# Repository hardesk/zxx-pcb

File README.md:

# Caravel with Z80 to DIP40 adapter PCB

See: https://github.com/rejunity/z80-open-silicon

## Pinout

                                   Z80 CPU
                   ,----------------.___.----------------.
      <--    A11  1| io[19] 57                 55 io[18] |40 A10    -->
      <--    A12  2| io[20] 58                 54 io[17] |39 A9     -->
      <--    A13  3| io[21] 59                 53 io[16] |38 A8     -->
      <--    A14  4| io[22] 60                 51 io[15] |37 A7     -->
      <--    A15  5| io[23] 61                 50 io[14] |36 A6     -->
      -->    CLK  6|  XCLK  22                 48 io[13] |35 A5     -->
      <->     D4  7| io[24] 62                 42 io[ 8] |34 A4     -->
      <->     D3  8| io[25]  2                 43 io[ 9] |33 A3     -->
      <->     D5  9| io[26]  3                 44 io[10] |32 A2     -->
      <->     D6 10| io[27]  4                 46 io[12] |31 A1     -->
         VCC_5V0 11|               Caravel     45 io[11] |30 A0     -->
      <->     D2 12| io[28]  5       pins                |29 GND
      <->     D7 13| io[29]  6                 41 io[ 7] |28 /RFSH  -->
      <->     D0 14| io[31]  8                 33 io[ 2] |27 /M1    -->
      <->     D1 15| io[30]  7                 21 io[ 0] |26 /RESET <--
      -->   /INT 16| io[33] 12                 34 io[37] |25 /BUSRQ <--
      -->   /NMI 17| io[32] 11                 37 io[ 6] |24 /WAIT  <--
      <--  /HALT 18| io[34] 31                 32 io[ 1] |23 /BUSAK -->
      <--  /MREQ 19| io[35] 13                 36 io[ 5] |22 /WR    -->
      <--  /IORQ 20| io[36] 14                 35 io[ 4] |21 /RD    -->
                   `-------------------------------------'

## Power rails for Caravel
        GND     29 (Z80) --- vss*               56, 52, 38, 39, 29, 23, 20, 10, 1
        VCC_5V0 11 (Z80) --- vddio              64, 17
        VCC_1V8    (LDO) --- vccd, vccd1, vccd2 63, 49, 18

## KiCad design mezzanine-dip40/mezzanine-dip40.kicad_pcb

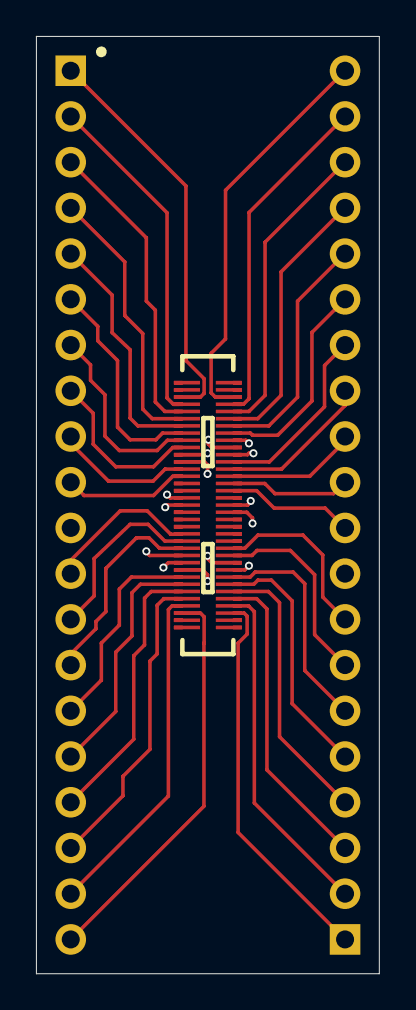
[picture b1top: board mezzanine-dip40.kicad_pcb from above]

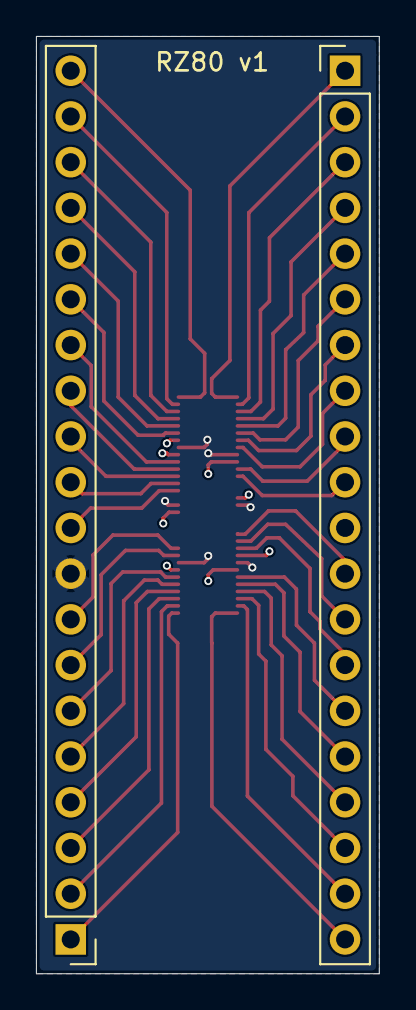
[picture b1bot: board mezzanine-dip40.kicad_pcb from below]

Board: 4 copper layers, 19.0 x 52.1 mm, 3 parts (2 on the bottom side), 40 nets.

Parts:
J1, J2: Conn_01x20; PinHeader_1x20_P2.54mm_Vertical
U2: CONN-SMD_70P-P0.40_HCTL_HC-PBB40C-70DS-0.4V-xx-02

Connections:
A_{0}: J2.10, U2.51 (pad_28)
A_{1}: J2.11, U2.50 (pad_29)
A_{2}: J2.12, U2.49 (pad_30)
A_{3}: J2.13, U2.48 (pad_31)
A_{4}: J2.14, U2.47 (pad_32)
A_{5}: J2.15, U2.43 (pad_37)
A_{6}: J2.16, U2.42 (pad_38)
A_{7}: J2.17, U2.41 (pad_39)
A_{8}: J2.18, U2.40 (pad_40)
A_{9}: J2.19, U2.39 (pad_41)
A_{10}: J2.20, U2.38 (pad_42)
A_{11}: J1.1, U2.33 (pad_48)
A_{12}: J1.2, U2.32 (pad_49)
A_{13}: J1.3, U2.31 (pad_50)
A_{14}: J1.4, U2.30 (pad_51)
A_{15}: J1.5, U2.29 (pad_52)
CLK: J1.6, U2.28 (pad_53)
D_{0}: J1.14, U2.12 (pad_69)
D_{1}: J1.15, U2.8 (pad_0)
D_{2}: J1.12, U2.14 (pad_67)
D_{3}: J1.8, U2.26 (pad_55)
D_{4}: J1.7, U2.27 (pad_54)
D_{5}: J1.9, U2.23 (pad_58)
D_{6}: J1.10, U2.22 (pad_59)
D_{7}: J1.13, U2.13 (pad_68)
GND: J2.9, U2.10 (GND), U2.18 (GND), U2.25 (GND), U2.45 (GND), U2.53 (GND), U2.61 (GND)
VCC: J1.11, U2.9 (VDD_IO), U2.11 (VDD_CORE), U2.19 (PWR_AUX), U2.24 (VDD_IO), U2.44 (VDD_IO), U2.46 (VDD_CORE), U2.54 (PWR_AUX), U2.62 (VDD_IO)
~BUSACK: J2.3, U2.66 (pad_13)
~BUSRQ: J2.5, U2.64 (pad_15)
~HALT: J1.18, U2.5 (pad_3)
~INT: J1.16, U2.7 (pad_1)
~IORQ: J1.20, U2.3 (pad_5)
~M1: J2.7, U2.60 (pad_19)
~MREQ: J1.19, U2.4 (pad_4)
~NMI: J1.17, U2.6 (pad_2)
~RD: J2.1, U2.68 (pad_11)
~RESET: J2.6, U2.63 (pad_16)
~RFSH: J2.8, U2.59 (pad_20)
~WAIT: J2.4, U2.65 (pad_14)
~WR: J2.2, U2.67 (pad_12)

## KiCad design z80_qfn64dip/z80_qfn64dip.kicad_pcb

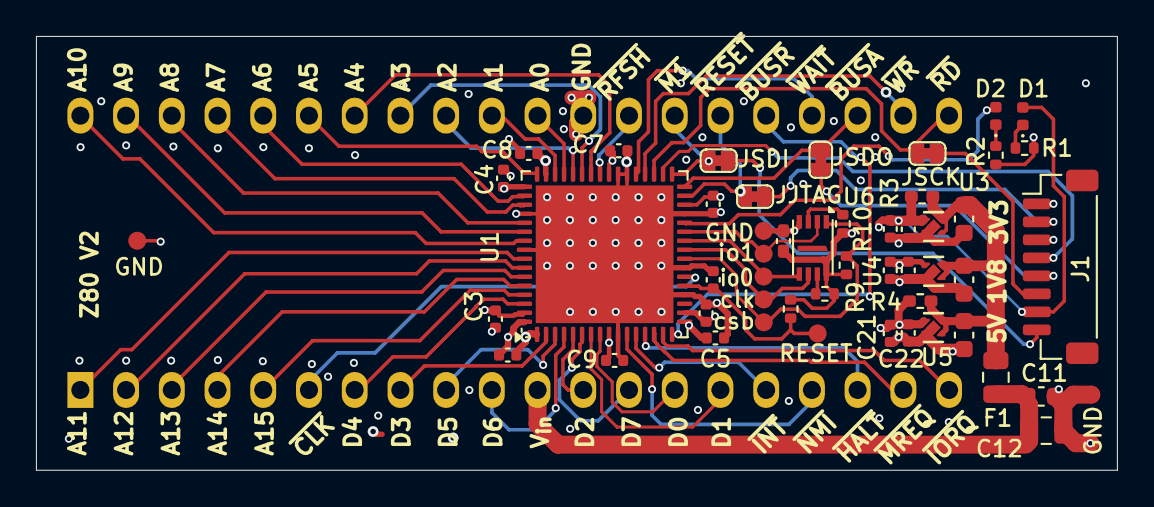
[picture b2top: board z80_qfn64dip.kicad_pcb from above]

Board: 4 copper layers, 60.1 x 24.1 mm, 52 parts (0 on the bottom side), 59 nets.

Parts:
C2, C3, C4, C5, C6, C7, C8, C9, C10, C18, C22, C26: 100nF; C_0402_1005Metric
C11: 10uF; C_0805_2012Metric
C12: 100nF; C_0603_1608Metric
C16, C23, C24: 4.7uF; C_0603_1608Metric
C17, C21, C25: 4.7uF; C_0402_1005Metric
C19: 1uF; C_0402_1005Metric
C20: 100nF; C_0402_1005Metric_Pad0.74x0.62mm_HandSolder
D1, D2: LED; LED_0402_1005Metric
F1: 350mA; Fuse_0805_2012Metric
J1: Conn_08; JST_SH_BM08B-SRSS-TB_1x08-1MP_P1.00mm_Vertical
JP1: JSDI; SolderJumper-2_P1.3mm_Bridged_RoundedPad1.0x1.5mm_Small_Mar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
JP2: JSCK; SolderJumper-2_P1.3mm_Bridged_RoundedPad1.0x1.5mm_Small_Mar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
JP3: JJTAG; SolderJumper-2_P1.3mm_Bridged_RoundedPad1.0x1.5mm_Small_Mar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
JP5: JSDO; SolderJumper-2_P1.3mm_Bridged_RoundedPad1.0x1.5mm_Small_Mar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
R1, R2: 4k7; R_0402_1005Metric
R3, R4: 0R; R_0402_1005Metric_Pad0.72x0.64mm_HandSolder
R9, R10, R11, R12: 10k; R_0402_1005Metric
TP9: io1; TestPoint_Pad_D1.0mm
TP10: io0; TestPoint_Pad_D1.0mm
TP11: clk; TestPoint_Pad_D1.0mm
TP12: csb; TestPoint_Pad_D1.0mm
TP13: GND; TestPoint_Pad_D1.0mm
TP14: RESET; TestPoint_Pad_D1.0mm_Small_Margin
TP15, TP16: GND; TestPoint_Pad_D1.0mm_Small_Margin
U1: Caravel_QFN; QFN-64-1EP_9x9mm_P0.5mm_EP7.65x7.65mm
U2: Z80CPU; IC_ADAPTER_ 220-1-40-006
U3: TPS7A2033PDQNRM3; DQN0004A-MFG
U4: TPS7A2018PDQNRM3; DQN0004A-MFG
U5: TPS7A2050PDQNRM3; DQN0004A-MFG
U6: AT25EU0081A; UDFN-8-1EP-2x3mm_P0.5mm_EP1.6x0.2mm

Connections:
/HKJTAG: J1.2, JP3.2 (B)
/HKSCK: J1.6, JP2.2 (B)
/HKSDI: J1.8, JP1.2 (B)
/HKSDO: J1.5, JP5.1 (A)
/VIN: C11.1, C12.1, F1.1, U2.11 (VCC)
/VIN_{F}: C16.1, C23.1, C24.1, F1.2, R3.1, R4.1, U3.3 (EN), U3.4 (IN), U4.3 (EN), U4.4 (IN), U5.3 (EN), U5.4 (IN)
/prj_io7: U1.41 (mprj_io[7]), U2.28 (~RFSH)
/prj_io8: U1.42 (mprj_io[8]), U2.34 (A4)
/prj_io9: U1.43 (mprj_io[9]), U2.33 (A3)
/prj_io10: U1.44 (mprj_io[10]), U2.32 (A2)
/prj_io11: U1.45 (mprj_io[11]), U2.30 (A0)
/prj_io12: U1.46 (mprj_io[12]), U2.31 (A1)
/prj_io13: U1.48 (mprj_io[13]), U2.35 (A5)
/prj_io14: U1.50 (mprj_io[14]), U2.36 (A6)
/prj_io15: U1.51 (mprj_io[15]), U2.37 (A7)
/prj_io16: U1.53 (mprj_io[16]), U2.38 (A8)
/prj_io17: U1.54 (mprj_io[17]), U2.39 (A9)
/prj_io18: U1.55 (mprj_io[18]), U2.40 (A10)
/prj_io19: U1.57 (mprj_io[19]), U2.1 (A11)
/prj_io20: U1.58 (mprj_io[20]), U2.2 (A12)
/prj_io21: U1.59 (mprj_io[21]), U2.3 (A13)
/prj_io22: U1.60 (mprj_io[22]), U2.4 (A14)
/prj_io23: U1.61 (mprj_io[23]), U2.5 (A15)
/prj_io24: U1.62 (mprj_io[24]), U2.7 (D4)
/prj_io25: U1.2 (mprj_io[25]), U2.8 (D3)
/prj_io26: U1.3 (mprj_io[26]), U2.9 (D5)
/prj_io27: U1.4 (mprj_io[27]), U2.10 (D6)
/prj_io28: U1.5 (mprj_io[28]), U2.12 (D2)
/prj_io29: U1.6 (mprj_io[29]), U2.13 (D7)
/prj_io30: U1.7 (mprj_io[30]), U2.15 (D1)
/prj_io31: U1.8 (mprj_io[31]), U2.14 (D0)
/prj_io32: U1.11 (mprj_io[32]), U2.17 (~NMI)
/prj_io33: U1.12 (mprj_io[33]), U2.16 (~INT)
/prj_io34: U1.13 (mprj_io[34]), U2.18 (~HALT)
/prj_io35: U1.14 (mprj_io[35]), U2.19 (~MREQ)
/prj_io36: U1.15 (mprj_io[36]), U2.20 (~IORQ)
/prj_io37: U1.16 (mprj_io[37]), U2.25 (~BUSRQ)
GND: C2.2, C3.1, C4.2, C5.1, C6.2, C7.2, C8.2, C9.2, C10.1, C11.2, C12.2, C16.2, C17.2, C18.2, C19.2, C20.2, C21.2, C22.2, C23.2, C24.2, C25.2, C26.2, J1.1, J1.3, R1.2, R2.2, TP13.1, TP15.1, TP16.1, U1.1 (vssa2), U1.10 (vssd2), U1.20 (vssa), U1.23 (vssd), U1.29 (vssio), U1.38 (vssa1), U1.39 (vssd1), U1.52 (vssa1), U1.56 (vssio), U1.65 (ThermalPad), U2.29 (GND), U3.2 (GND), U3.5 (Thermal_Pad), U4.2 (GND), U4.5 (Thermal_Pad), U5.2 (GND), U5.5 (Thermal_Pad), U6.4 (GND)
HK_CSB: J1.4, U1.34 (mprj_io[3]_CSB)
HK_JTAG: JP3.1 (A), U1.31 (mprj_io[0]_JTAG), U2.26 (~RESET)
HK_SCK: JP2.1 (A), U1.35 (mprj_io[4]_SCK), U2.21 (~RD)
HK_SDI: JP1.1 (A), U1.33 (mprj_io[2]_SDI), U2.27 (~M1)
HK_SDO: JP5.2 (B), U1.32 (mprj_io[1]_SDO), U2.23 (~BUSACK)
unnamed: D1.1 (K), R1.1
unnamed: D2.1 (K), R2.1
unnamed: R11.1, U6.7 (~HOLD(IO_{3}))
unnamed: R10.1, U6.3 (~WP(IO_{2}))
VCCD: C2.1, C3.2, C4.1, C17.1, C18.1, U1.18 (vccd), U1.49 (vccd1), U1.63 (vccd2), U4.1 (OUT)
VDDA: C6.1, C7.1, C8.1, C9.1, C20.1, C25.1, C26.1, D1.2 (A), J1.7, R3.2, R9.1, R10.2, R11.2, R12.1, U1.9 (vdda2), U1.30 (vdda), U1.40 (vdda1), U1.47 (vdda1), U3.1 (OUT), U6.8 (Vcc)
VDDIO: C5.2, C10.2, C21.1, C22.1, R4.2, U1.17 (vddio), U1.64 (vddio), U5.1 (OUT)
flash_clk: TP11.1, U1.25 (flash_clk), U6.6 (SCK)
flash_csb: R9.2, TP12.1, U1.24 (flash_csb), U6.1 (~CS)
flash_io0: TP10.1, U1.26 (flash_io0), U6.5 (SI(IO_{0}))
flash_io1: TP9.1, U1.27 (flash_io1), U6.2 (SO(IO_{1}))
gpio: D2.2 (A), U1.28 (gpio)
osc_out: U1.22 (clock), U2.6 (~CLK)
ser_rx: U1.36 (mprj_io[5]_ser_rx), U2.22 (~WR)
ser_tx: U1.37 (mprj_io[6]_ser_tx), U2.24 (~WAIT)
~SOC_RST: C19.1, R12.2, TP14.1, U1.21 (resetb)

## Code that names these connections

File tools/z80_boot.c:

#include <defs.h>
#include <stub.h>

#define NOPULL

#define reg_mprj_proj_sel (*(volatile uint32_t*)0x30100004)
#define reg_mprj_counter (*(volatile uint32_t*)0x30100008)
#define reg_mprj_settings (*(volatile uint32_t*)0x3010000C)

#define FREQ_CPU 7550000

//#define EARLY_SIGNALS

void delay(const unsigned d) {
	#if 1

	reg_timer0_config = 0;			// disable timer
	reg_timer0_data = d;			// load the start value
	reg_timer0_data_periodic = 0u;
	reg_timer0_irq_en = 0;
	reg_timer0_config = 1;			// enable timer

	do { 
		reg_timer0_update = 1;
		//reg_gpio_out = (reg_timer0_value >> 31) & 1;

		// on the chip at hand it appears that the timer does not stop at 0. check underflow manually
	} while (reg_timer0_value > 0 && reg_timer0_value <= d);

	#else
    for(uint64_t i=d>>2; i-- > 0; )
        (void)0;
	#endif
}

#define DELAY_US(us) delay(FREQ_CPU / 1000000 * (us))
#define DELAY_MS(ms) delay(FREQ_CPU / 1000 * (ms))

// this only works in -O0 builds
void ldelay(int d) {
    for(uint64_t i=d>>2; i-- > 0; )
        (volatile void)0;
}

void configure_io() {

#ifdef NOPULL
	// Pins [1-4] are used for flashing. If not INPUT, the setting will interfere with data transfer. If so,
	// keep RESET (of SOC) active while accessing the flash.
	reg_mprj_io_0 = GPIO_MODE_USER_STD_INPUT_NOPULL;	// /RESET
	reg_mprj_io_1 = GPIO_MODE_USER_STD_OUTPUT;			// /BUSACK [HK_SDO]
	reg_mprj_io_2 = GPIO_MODE_USER_STD_OUTPUT;			// /M1 [HK_SDI]
	reg_mprj_io_3 = GPIO_MODE_USER_STD_INPUT_NOPULL;	// [HK_CSB]
	reg_mprj_io_4 = GPIO_MODE_USER_STD_OUTPUT;			// /RD + [HK_SCK]
	reg_mprj_io_5 = GPIO_MODE_USER_STD_OUTPUT;			// /WR + [ser_rx]
	reg_mprj_io_6 = GPIO_MODE_USER_STD_INPUT_NOPULL;	// /WAIT + [ser_tx]
	reg_mprj_io_7 = GPIO_MODE_USER_STD_OUTPUT;			// /RFSH

	// io8:io23 -> A0:A15
	reg_mprj_io_8 = GPIO_MODE_USER_STD_OUTPUT;
	reg_mprj_io_9 = GPIO_MODE_USER_STD_OUTPUT;
	reg_mprj_io_10 = GPIO_MODE_USER_STD_OUTPUT;
	reg_mprj_io_11 = GPIO_MODE_USER_STD_OUTPUT;
	reg_mprj_io_12 = GPIO_MODE_USER_STD_OUTPUT;
	reg_mprj_io_13 = GPIO_MODE_USER_STD_OUTPUT;
	reg_mprj_io_14 = GPIO_MODE_USER_STD_OUTPUT;
	reg_mprj_io_15 = GPIO_MODE_USER_STD_OUTPUT;
	reg_mprj_io_16 = GPIO_MODE_USER_STD_OUTPUT;
	reg_mprj_io_17 = GPIO_MODE_USER_STD_OUTPUT;
	reg_mprj_io_18 = GPIO_MODE_USER_STD_OUTPUT;
	reg_mprj_io_19 = GPIO_MODE_USER_STD_OUTPUT;
	reg_mprj_io_20 = GPIO_MODE_USER_STD_OUTPUT;
	reg_mprj_io_21 = GPIO_MODE_USER_STD_OUTPUT;
	reg_mprj_io_22 = GPIO_MODE_USER_STD_OUTPUT;
	reg_mprj_io_23 = GPIO_MODE_USER_STD_OUTPUT;
	// io24:io31 -> D0:D7
	reg_mprj_io_24 = GPIO_MODE_USER_STD_BIDIRECTIONAL;
	reg_mprj_io_25 = GPIO_MODE_USER_STD_BIDIRECTIONAL;
	reg_mprj_io_26 = GPIO_MODE_USER_STD_BIDIRECTIONAL;
	reg_mprj_io_27 = GPIO_MODE_USER_STD_BIDIRECTIONAL;
	reg_mprj_io_28 = GPIO_MODE_USER_STD_BIDIRECTIONAL;
	reg_mprj_io_29 = GPIO_MODE_USER_STD_BIDIRECTIONAL;
	reg_mprj_io_30 = GPIO_MODE_USER_STD_BIDIRECTIONAL;
	reg_mprj_io_31 = GPIO_MODE_USER_STD_BIDIRECTIONAL;

	reg_mprj_io_32 = GPIO_MODE_USER_STD_INPUT_NOPULL;	// /NMI
	reg_mprj_io_33 = GPIO_MODE_USER_STD_INPUT_NOPULL;	// /INT
	reg_mprj_io_34 = GPIO_MODE_USER_STD_OUTPUT;			// /HALT
	reg_mprj_io_35 = GPIO_MODE_USER_STD_OUTPUT;			// /MREQ
	reg_mprj_io_36 = GPIO_MODE_USER_STD_OUTPUT;			// /IORQ
	reg_mprj_io_37 = GPIO_MODE_USER_STD_INPUT_NOPULL;	// /BUSRQ
#else
	reg_mprj_io_0 = GPIO_MODE_USER_STD_INPUT_PULLUP;
	reg_mprj_io_1 = GPIO_MODE_USER_STD_OUTPUT;
	reg_mprj_io_2 = GPIO_MODE_USER_STD_OUTPUT;
	reg_mprj_io_3 = GPIO_MODE_MGMT_STD_INPUT_PULLUP;
	reg_mprj_io_4 = GPIO_MODE_USER_STD_OUTPUT;
	
	reg_mprj_io_5 = GPIO_MODE_USER_STD_OUTPUT;
	reg_mprj_io_6 = GPIO_MODE_USER_STD_INPUT_PULLUP;
	reg_mprj_io_7 = GPIO_MODE_USER_STD_OUTPUT;
	reg_mprj_io_8 = GPIO_MODE_USER_STD_OUTPUT;
	reg_mprj_io_9 = GPIO_MODE_USER_STD_OUTPUT;
	reg_mprj_io_10 = GPIO_MODE_USER_STD_OUTPUT;
	reg_mprj_io_11 = GPIO_MODE_USER_STD_OUTPUT;
	reg_mprj_io_12 = GPIO_MODE_USER_STD_OUTPUT;
	reg_mprj_io_13 = GPIO_MODE_USER_STD_OUTPUT;
	reg_mprj_io_14 = GPIO_MODE_USER_STD_OUTPUT;
	reg_mprj_io_15 = GPIO_MODE_USER_STD_OUTPUT;
	reg_mprj_io_16 = GPIO_MODE_USER_STD_OUTPUT;
	reg_mprj_io_17 = GPIO_MODE_USER_STD_OUTPUT;
	reg_mprj_io_18 = GPIO_MODE_USER_STD_OUTPUT;
	reg_mprj_io_19 = GPIO_MODE_USER_STD_OUTPUT;
	reg_mprj_io_20 = GPIO_MODE_USER_STD_OUTPUT;
	reg_mprj_io_21 = GPIO_MODE_USER_STD_OUTPUT;
	reg_mprj_io_22 = GPIO_MODE_USER_STD_OUTPUT;
	reg_mprj_io_23 = GPIO_MODE_USER_STD_OUTPUT;
	reg_mprj_io_24 = GPIO_MODE_USER_STD_BIDIRECTIONAL;
	reg_mprj_io_25 = GPIO_MODE_USER_STD_BIDIRECTIONAL;
	reg_mprj_io_26 = GPIO_MODE_USER_STD_BIDIRECTIONAL;
	reg_mprj_io_27 = GPIO_MODE_USER_STD_BIDIRECTIONAL;
	reg_mprj_io_28 = GPIO_MODE_USER_STD_BIDIRECTIONAL;
	reg_mprj_io_29 = GPIO_MODE_USER_STD_BIDIRECTIONAL;
	reg_mprj_io_30 = GPIO_MODE_USER_STD_BIDIRECTIONAL;
	reg_mprj_io_31 = GPIO_MODE_USER_STD_BIDIRECTIONAL;
	reg_mprj_io_32 = GPIO_MODE_USER_STD_INPUT_PULLUP;
	reg_mprj_io_33 = GPIO_MODE_USER_STD_INPUT_PULLUP;
	reg_mprj_io_34 = GPIO_MODE_USER_STD_OUTPUT;
	reg_mprj_io_35 = GPIO_MODE_USER_STD_OUTPUT;
	reg_mprj_io_36 = GPIO_MODE_USER_STD_OUTPUT;
	reg_mprj_io_37 = GPIO_MODE_USER_STD_INPUT_PULLUP;
#endif
    reg_mprj_xfer = 1;
    while (reg_mprj_xfer == 1); // this condition works, tested
}

void main() {

	reg_wb_enable = 1;
	reg_uart_enable = 0;
	reg_gpio_mode1 = 1;
	reg_gpio_mode0 = 0;
	reg_gpio_ien = 1;
	reg_gpio_oe = 1;

	for (int i=3; i --> 0; ) {
		reg_gpio_out = 1;
		DELAY_MS(80);
		reg_gpio_out = 0;
		DELAY_MS(80);
	}

	reg_mprj_counter = 0;
	configure_io();

	reg_spi_enable = 0;

    reg_mprj_proj_sel = 0b00101;
#ifdef EARLY_SIGNALS
	reg_mprj_settings = 1+65536;
#else
	reg_mprj_settings = 65536;
#endif
	reg_mprj_proj_sel = 0b00100;

	unsigned cycle = 0;
	while(1) {
		unsigned dels[] = { FREQ_CPU / 1000 * 40, FREQ_CPU / 1000 * 80, FREQ_CPU / 1000 * 70, FREQ_CPU / 1000 * 650 };

		unsigned x = cycle & 3;
		unsigned l = 1 - (cycle & 1);

        reg_gpio_out = l;
		delay(dels[x]);

		cycle++;
	}
}

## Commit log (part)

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2024-05-29 pcb 2 layer
2024-05-30 Pin connections
2024-05-31 add flash and move to 4 layers
2024-06-02 hand solder pads for bottom caps, minor tweaks to layout
2024-06-03 jtag/spi connector
2024-06-05 remove crystal; testpoints connected directly to flash
2024-06-05 tweak connections due to changed caravel pinout
2024-06-06 update readme pin numbers
2025-05-17 layout tweaks, update to kicad 9
2025-05-22 routed and DRC mostly checked
2025-05-22 add zero-ohm resistor for VDDIO as well, fill B with ground, minor changes
2025-05-28 minor layout position tweaks; move schematics around a bit; add aisler user design rule
2025-05-29 remove signals from power layer moving them to bottom layer; change power routing from tracks to planes if they can be called as such
2025-06-03 minor changes
2025-07-14 mainly layout changes, remove kicad_prl from comitted files
2025-07-14 move everything to front side; label pins
2025-10-29 rp2350 driver build files
2025-10-29 pcb: kicad symbols
2025-11-05 building a rp2350 driver using cmake
2025-11-06 fix linker script to correctly put crt code at the beginning. z80_boot blinks a pio_led now
2025-11-29 fix boot: move crt code to .text.crt0 section to actually make it first in ELF, workaround for a seemingly faulty timer0, copy isr.c. Blinking with style
2025-12-03 fix assembler invocation. default lax parsing would incorrectly parse 'and a, x' instructions into two. fixes and printint support on IORQ/WR
2025-12-03 something like a ram-test. ported prelim_test and a cpm-style print basic test
2025-12-11 rp2350_driver: DeZog vscode launcher, load code at 0x8000, sjasm support (need to comment/uncomment to switch)
2026-06-14 mezzanine hcl connector to DIP40 adapter
